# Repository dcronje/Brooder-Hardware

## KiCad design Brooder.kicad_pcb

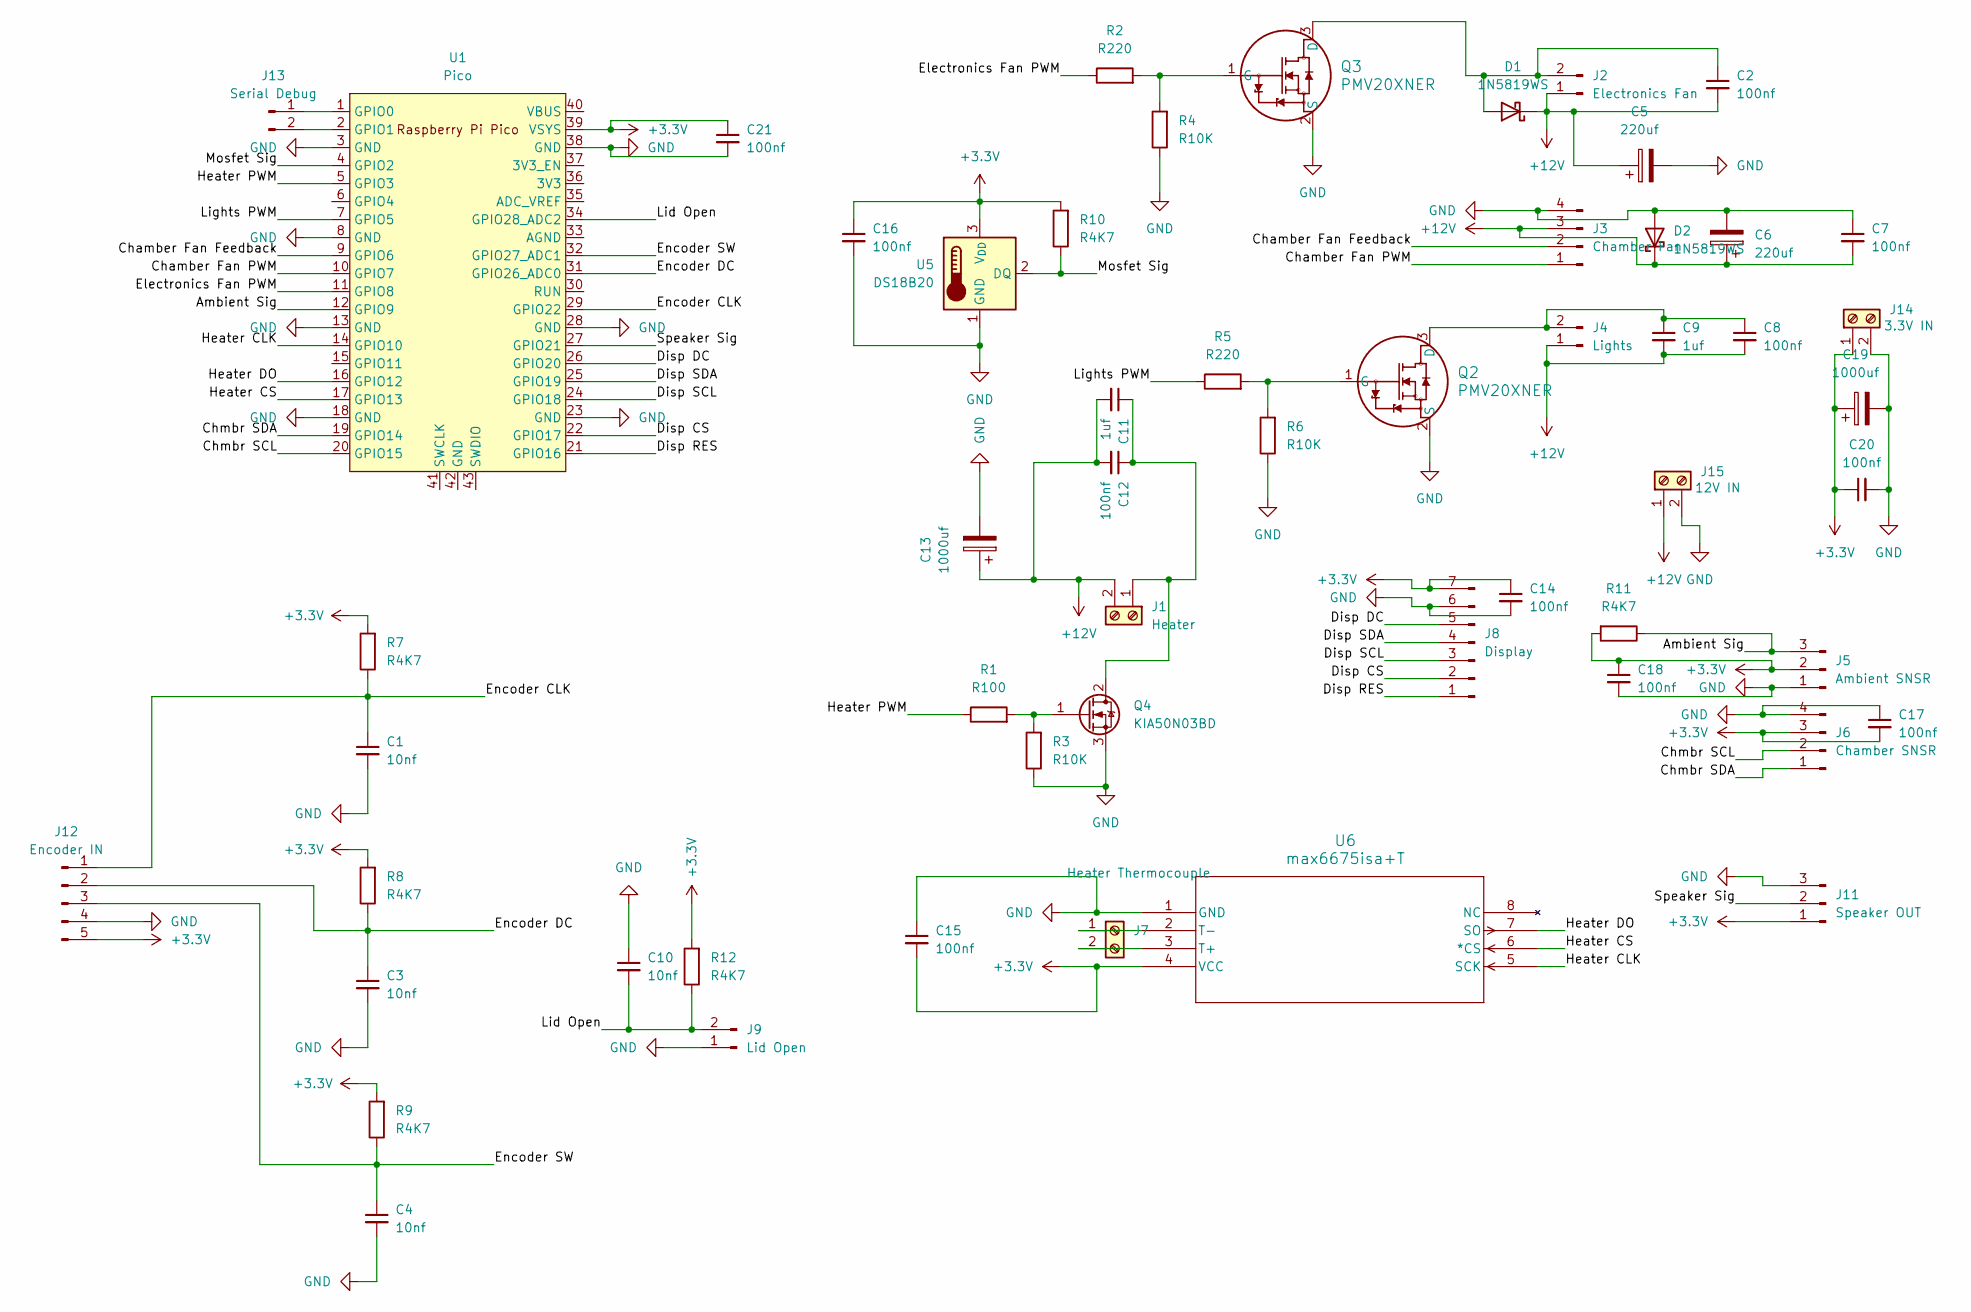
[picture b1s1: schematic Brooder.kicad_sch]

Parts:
C1, C3, C4, C10: 10nf; C_1206_3216Metric
C2, C7, C8, C12, C14, C15, C16, C17, C18, C20, C21: 100nf; C_1210_3225Metric
C5, C6: 220uf; CP_Elec_8x10.5
C9, C11: 1uf; C_1210_3225Metric
C13, C19: 1000uf; CP_Elec_10x10.5
D1, D2: 1N5819WS; D_SOD-323
J1: Heater; TerminalBlock_MetzConnect_Type067_RT01902HDWC_1x02_P10.00mm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
J2: Electronics Fan; SMD-PinHeader_1x02_P2.54mm_Vertical
J3: Chamber Fan; SMD-PinHeader_1x04_P2.54mm_Vertical
J4: Lights; SMD-PinHeader_1x02_P2.54mm_Vertical
J5: Ambient SNSR; SMD-PinHeader_1x03_P2.54mm_Vertical
J6: Chamber SNSR; SMD-PinHeader_1x04_P2.54mm_Vertical
J7: Heater Thermocouple; TerminalBlock_MetzConnect_Type171_RT13702HBWC_1x02_P7.50mm_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
J8: Display; SMD-PinHeader_1x07_P2.54mm_Vertical
J9: Lid Open; SMD-PinHeader_1x02_P2.54mm_Vertical
J11: Speaker OUT; SMD-PinHeader_1x03_P2.54mm_Vertical
J12: Encoder IN; SMD-PinHeader_1x05_P2.54mm_Vertical
J13: Serial Debug; SMD-PinHeader_1x02_P2.54mm_Vertical
J14: 3.3V IN; TerminalBlock_bornier-2_P5.08mm
J15: 12V IN; TerminalBlock_MetzConnect_Type067_RT01902HDWC_1x02_P10.00mm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
Q2, Q3: PMV20XNER; SOT23-TO-236AB_NEX
Q4: KIA50N03BD; TO-252-2
R1: R100; R_1206_3216Metric
R2, R5: R220; R_1206_3216Metric
R3, R4, R6: R10K; R_1206_3216Metric
R7, R8, R9, R10, R11, R12: R4K7; R_1206_3216Metric
U1: Pico; RPi_Pico_SMD_TH
U5: DS18B20; DS18B20_SMD
U6: max6675isa+T; 21-0041B_8_MXM

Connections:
+3.3V: C14.1, C15.2, C16.1, C17.2, C18.1, C19.1, C20.1, C21.1, J5.2, J6.3, J8.7, J11.1, J12.5, J14.1, R7.2, R8.2, R9.2, R10.2, R11.2, R12.2, U1.39 (VSYS), U5.3 (V_{DD}), U6.4 (VCC)
+12V: C2.2, C5.1, C6.1, C7.2, C8.2, C9.2, C11.2, C12.2, C13.1, D1.1 (K), D2.1 (K), J1.2, J2.1, J3.3, J4.1, J15.1
/Ambient Sig: J5.3, R11.1, U1.12 (GPIO9)
/Chamber Fan Feedback: J3.2, U1.9 (GPIO6)
/Chamber Fan PWM: J3.1, U1.10 (GPIO7)
/Chmbr SCL: J6.2, U1.20 (GPIO15)
/Chmbr SDA: J6.1, U1.19 (GPIO14)
/Disp CS: J8.2, U1.22 (GPIO17)
/Disp DC: J8.5, U1.26 (GPIO20)
/Disp RES: J8.1, U1.21 (GPIO16)
/Disp SCL: J8.3, U1.24 (GPIO18)
/Disp SDA: J8.4, U1.25 (GPIO19)
/Electronics Fan PWM: R2.1, U1.11 (GPIO8)
/Encoder CLK: C1.1, J12.1, R7.1, U1.29 (GPIO22)
/Encoder DC: C3.1, J12.2, R8.1, U1.31 (GPIO26_ADC0)
/Encoder SW: C4.1, J12.3, R9.1, U1.32 (GPIO27_ADC1)
/Heater CLK: U1.14 (GPIO10), U6.5 (SCK)
/Heater CS: U1.17 (GPIO13), U6.6 (*CS)
/Heater DO: U1.16 (GPIO12), U6.7 (SO)
/Heater PWM: R1.1, U1.5 (GPIO3)
/Lid Open: C10.2, J9.2, R12.1, U1.34 (GPIO28_ADC2)
/Lights PWM: R5.1, U1.7 (GPIO5)
/Mosfet Sig: R10.1, U1.4 (GPIO2), U5.2 (DQ)
/Speaker Sig: J11.2, U1.27 (GPIO21)
GND: C1.2, C3.2, C4.2, C5.2, C6.2, C7.1, C10.1, C13.2, C14.2, C15.1, C16.2, C17.1, C18.2, C19.2, C20.2, C21.2, D2.2 (A), J3.4, J5.1, J6.4, J8.6, J9.1, J11.3, J12.4, J14.2, J15.2, Q2.2 (S), Q3.2 (S), Q4.3 (S), R3.1, R4.1, R6.1, U1.3 (GND), U1.8 (GND), U1.13 (GND), U1.18 (GND), U1.23 (GND), U1.28 (GND), U1.38 (GND), U5.1 (GND), U6.1 (GND)
unnamed: C2.1, D1.2 (A), J2.2, Q3.3 (D)
unnamed: C11.1, C12.1, J1.1, Q4.2 (D)
unnamed: C8.1, C9.1, J4.2, Q2.3 (D)
unnamed: J7.1, U6.2 (T-)
unnamed: J7.2, U6.3 (T+)
unnamed: J13.1, U1.1 (GPIO0)
unnamed: J13.2, U1.2 (GPIO1)
unnamed: Q2.1 (G), R5.2, R6.2
unnamed: Q3.1 (G), R2.2, R4.2
unnamed: Q4.1 (G), R1.2, R3.2

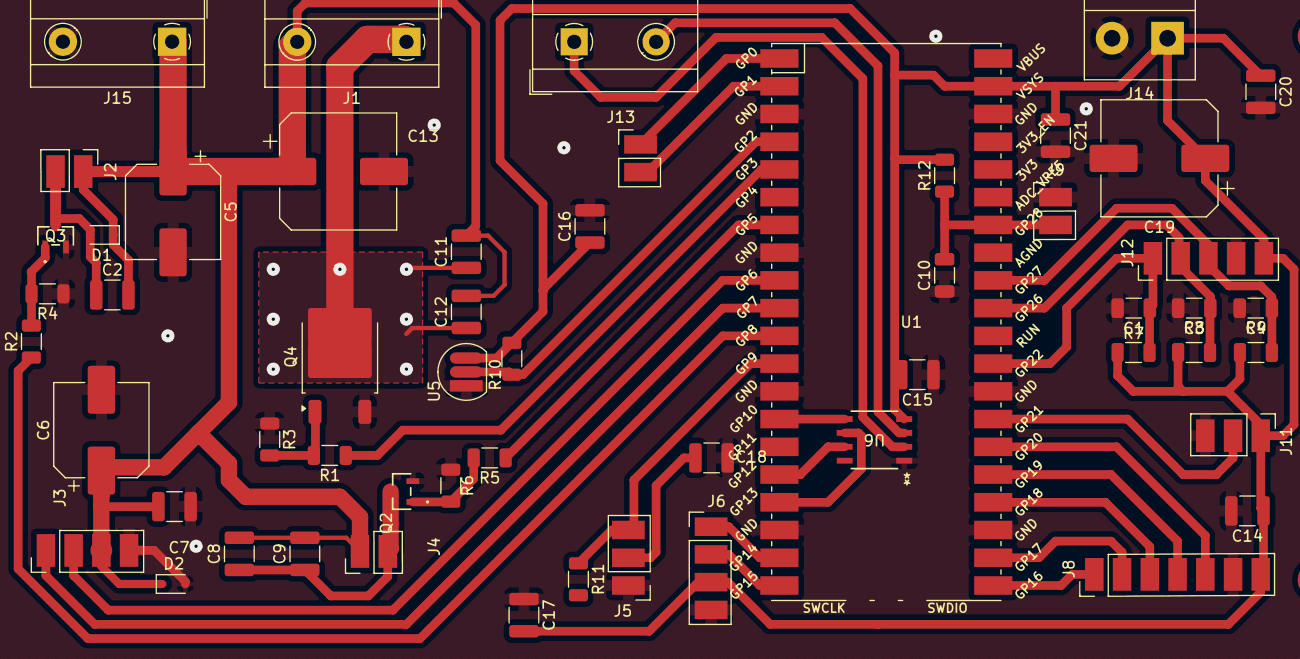
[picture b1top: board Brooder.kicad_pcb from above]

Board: 2 copper layers, 55 parts (0 on the bottom side), 35 nets.

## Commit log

2025-01-08 Initial
2025-01-09 Added diode to chamber fan
